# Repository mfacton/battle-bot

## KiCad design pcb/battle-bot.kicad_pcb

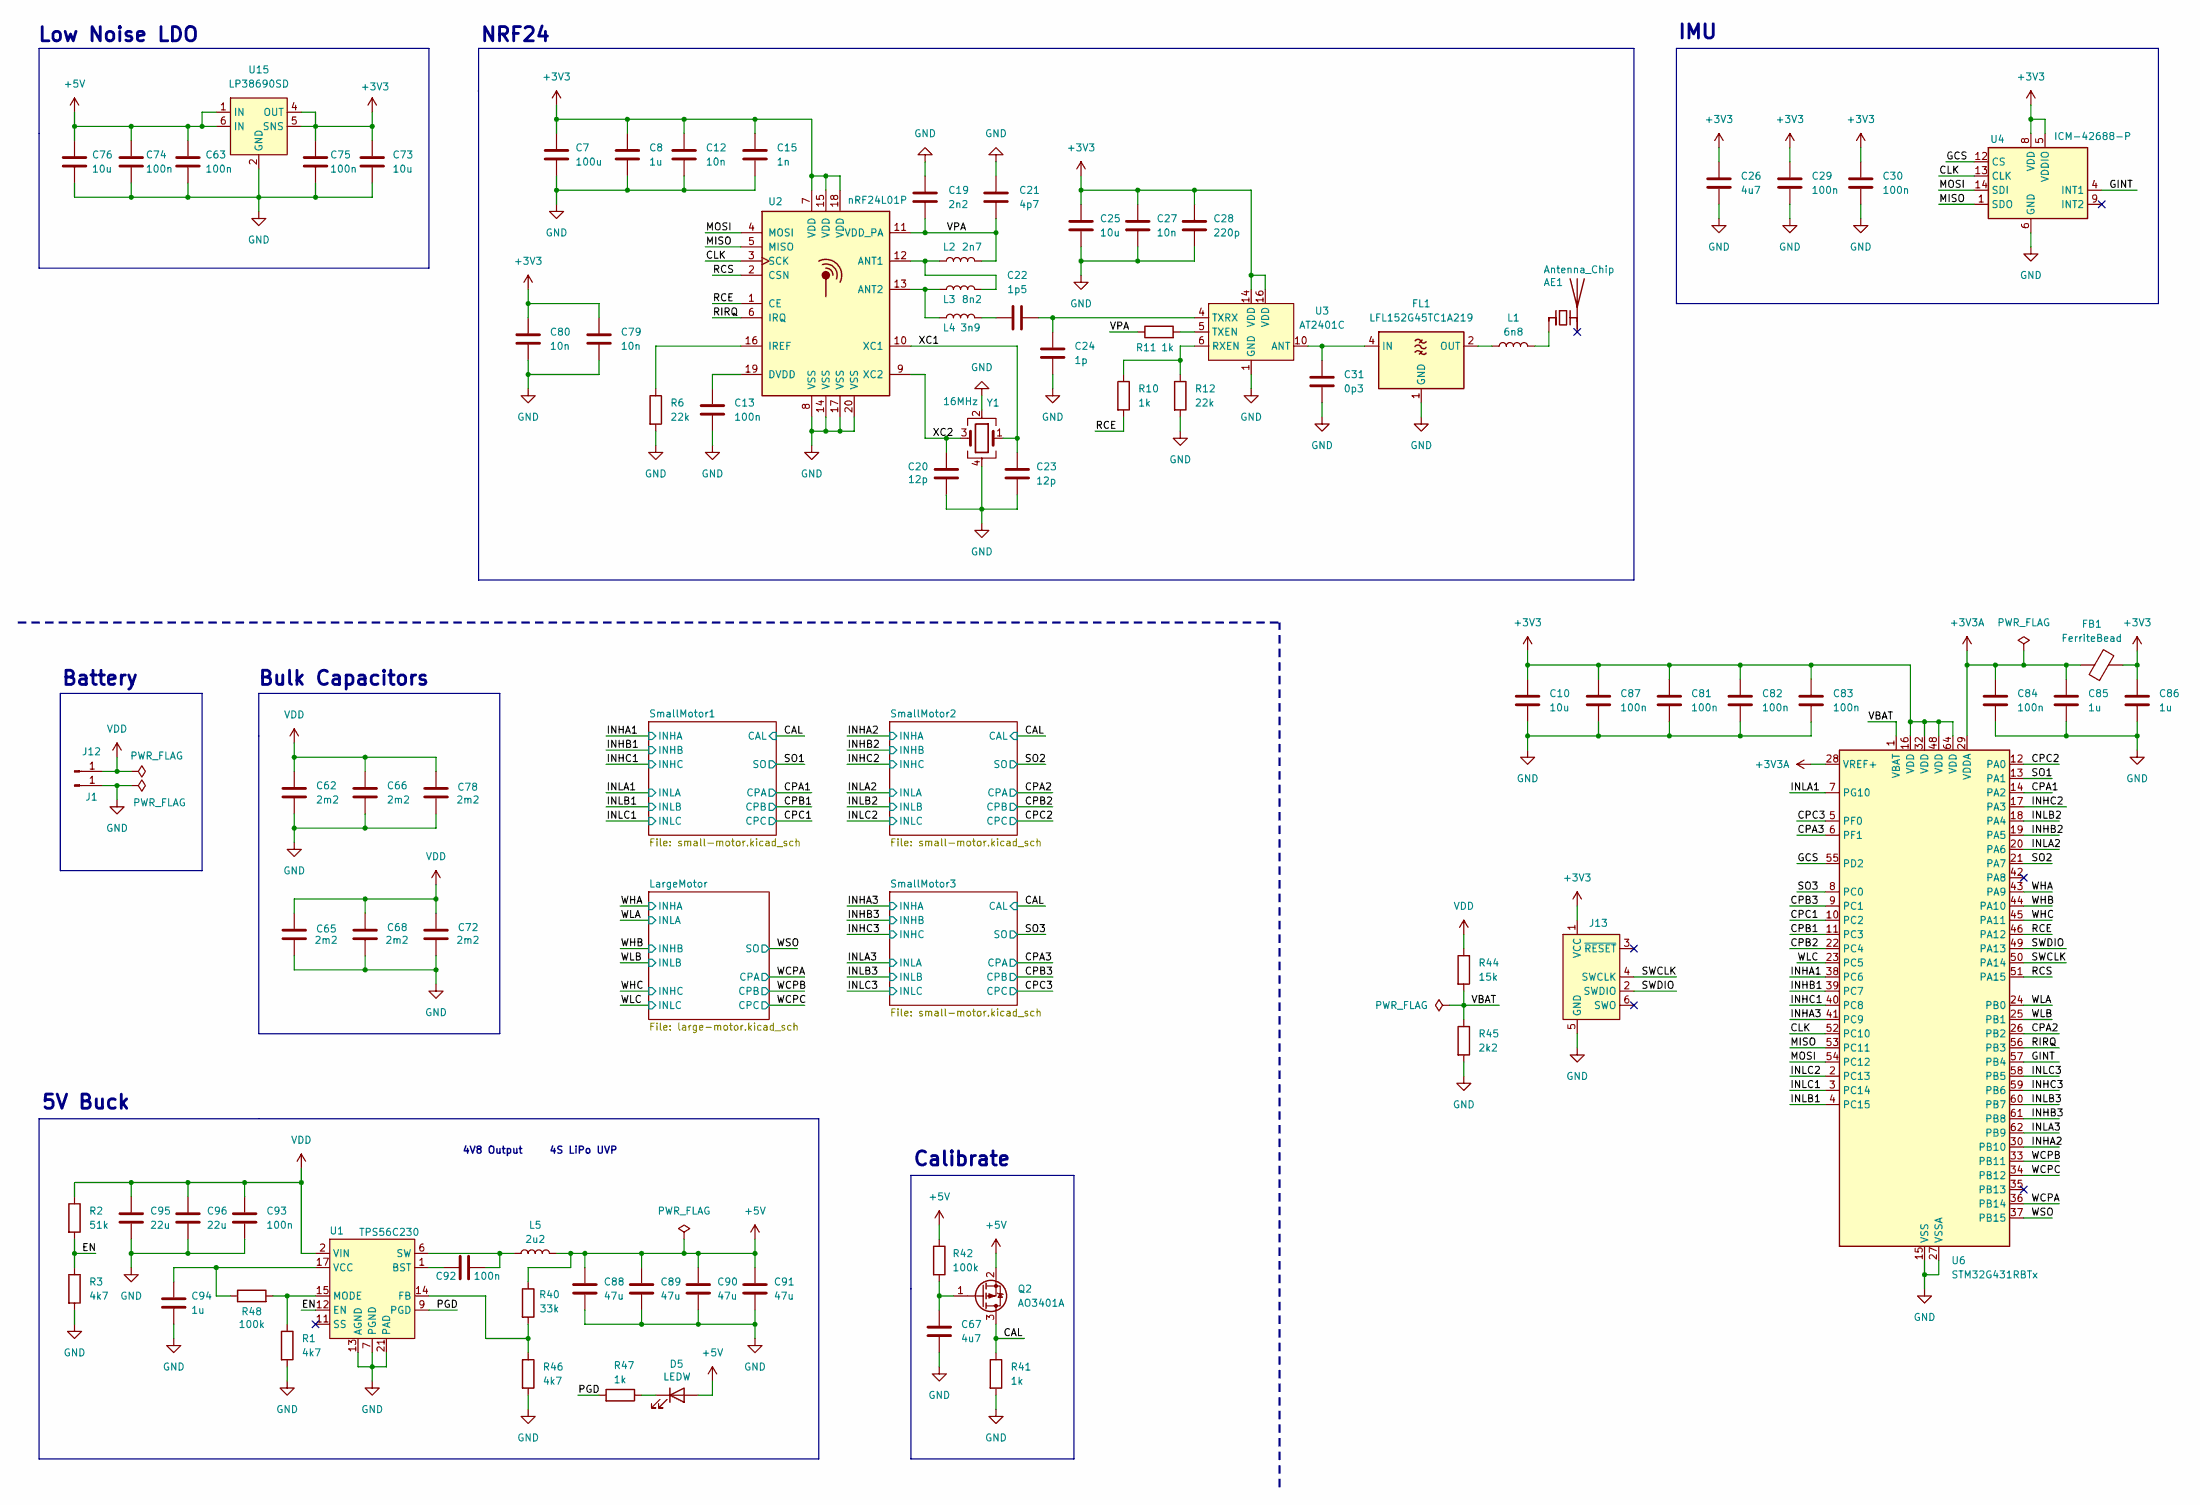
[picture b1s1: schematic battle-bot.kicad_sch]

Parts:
AE1: Antenna_Chip; Johanson_2450AT18x100; LCSC C127629
C7: 100u; C_1206_3216Metric; LCSC C15008
C8, C85, C86, C94: 1u; C_0402_1005Metric; LCSC C52923
C10, C25, C73: 10u; C_0402_1005Metric; LCSC C15525
C12, C27, C79, C80: 10n; C_0402_1005Metric; LCSC C15195
C13, C29, C30, C63, C74, C75, C81, C82, C83, C84, C87, C92: 100n; C_0402_1005Metric; LCSC C1525
C15: 1n; C_0402_1005Metric; LCSC C1523
C19: 2n2; C_0402_1005Metric; LCSC C1531
C20, C23: 12p; C_0402_1005Metric; LCSC C1547
C21: 4p7; C_0402_1005Metric; LCSC C1569
C22: 1p5; C_0402_1005Metric; LCSC C1552
C24: 1p; C_0402_1005Metric; LCSC C1550
C26, C67: 4u7; C_0402_1005Metric; LCSC C23733
C28: 220p; C_0402_1005Metric; LCSC C1530
C31: 0p3; C_0402_1005Metric; LCSC C880415
C62, C65, C66, C68, C72, C78: 2m2; C_D10xL16_Horizontal; LCSC C5438720
C76: 10u; C_0603_1608Metric; LCSC C19702
C88, C89, C90, C91: 47u; C_1206_3216Metric; LCSC C96123
C93: 100n; C_0402_1005Metric; LCSC C307331
C95, C96: 22u; C_0805_2012Metric; LCSC C45783
D5: LEDW; LED_0603_1608Metric; LCSC C2290
FB1: FerriteBead; L_0805_2012Metric; LCSC C1017
FL1: LFL152G45TC1A219; LCSC C91610
J1, J12: Conn_01x01_Pin; MountingHole_3.2mm_M3_Pad_Via
J13: Conn_ARM_SWD_TagConnect_TC2030-NL; Tag-Connect_TC2030-IDC-NL_2x03_P1.27mm_Vertical
L1: 6n8; L_0402_1005Metric; LCSC C82919
L2: 2n7; L_0402_1005Metric; LCSC C162541
L3: 8n2; L_0402_1005Metric; LCSC C84404
L4: 3n9; L_0402_1005Metric; LCSC C14033
L5: 2u2; L_Chilisin_BMRB00060618; LCSC C216189
Q2: AO3401A; SOT-23; LCSC C15127
R1, R3, R46: 4k7; R_0402_1005Metric; LCSC C25900
R2: 51k; R_0402_1005Metric; LCSC C25794
R6, R12: 22k; R_0402_1005Metric; LCSC C25768
R10, R11, R41, R47: 1k; R_0402_1005Metric; LCSC C11702
R40: 33k; R_0402_1005Metric; LCSC C25779
R42, R48: 100k; R_0402_1005Metric; LCSC C25741
R44: 15k; R_0402_1005Metric; LCSC C25756
R45: 2k2; R_0402_1005Metric; LCSC C25879
U1: TPS56C230; VQFN-20_3x3mm_P0.45; LCSC C1849534
U2: nRF24L01P; QFN-20-1EP_4x4mm_P0.5mm_EP2.5x2.5mm; LCSC C8791
U3: AT2401C; QFN-16-1EP_3x3mm_P0.5mm_EP1.7x1.7mm; LCSC C783588
U4: ICM-42688-P; LGA-14_3x2.5mm_P0.5mm_LayoutBorder3x4y
U6: STM32G431RBTx; LQFP-64_10x10mm_P0.5mm; LCSC C431633
U15: LP38690SD; DFN-6-1EP_3x3mm_P0.95mm_EP1.7x2.6mm; LCSC C130003
Y1: 16MHz; Crystal_SMD_3225-4Pin_3.2x2.5mm; LCSC C13738

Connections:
+3V3: C7.1, C8.1, C10.1, C12.1, C15.1, C25.1, C26.1, C27.1, C28.1, C29.1, C30.1, C73.1, C75.1, C79.1, C80.1, C81.1, C82.1, C83.1, C86.1, C87.1, FB1.2, J13.1 (VCC), U2.7 (VDD), U2.15 (VDD), U2.18 (VDD), U3.14 (VDD), U3.16 (VDD), U4.5 (VDDIO), U4.8 (VDD), U6.16 (VDD), U6.32 (VDD), U6.48 (VDD), U6.64 (VDD), U15.4 (OUT), U15.5 (SNS); also elsewhere on the board
+3V3A: C84.1, C85.1, FB1.1, U6.28 (VREF+), U6.29 (VDDA)
+5V: C63.1, C74.1, C76.1, C88.1, C89.1, C90.1, C91.1, D5.2 (A), L5.2, Q2.2 (S), R40.1, R42.1, U15.1 (IN), U15.6 (IN); also elsewhere on the board
/CAL: Q2.3 (D), R41.1; also elsewhere on the board
/CLK: U2.3 (SCK), U4.13 (CLK), U6.52 (PC10)
/CPA1: U6.14 (PA2); also elsewhere on the board
/CPA2: U6.26 (PB2); also elsewhere on the board
/CPA3: U6.6 (PF1); also elsewhere on the board
/CPB1: U6.11 (PC3); also elsewhere on the board
/CPB2: U6.22 (PC4); also elsewhere on the board
/CPB3: U6.9 (PC1); also elsewhere on the board
/CPC1: U6.10 (PC2); also elsewhere on the board
/CPC2: U6.12 (PA0); also elsewhere on the board
/CPC3: U6.5 (PF0); also elsewhere on the board
/EN: R2.2, R3.1, U1.12 (EN)
/GCS: U4.12 (CS), U6.55 (PD2)
/GINT: U4.4 (INT1), U6.57 (PB4)
/INHA1: U6.38 (PC6); also elsewhere on the board
/INHA2: U6.30 (PB10); also elsewhere on the board
/INHA3: U6.41 (PC9); also elsewhere on the board
/INHB1: U6.39 (PC7); also elsewhere on the board
/INHB2: U6.19 (PA5); also elsewhere on the board
/INHB3: U6.61 (PB8); also elsewhere on the board
/INHC1: U6.40 (PC8); also elsewhere on the board
/INHC2: U6.17 (PA3); also elsewhere on the board
/INHC3: U6.59 (PB6); also elsewhere on the board
/INLA1: U6.7 (PG10); also elsewhere on the board
/INLA2: U6.20 (PA6); also elsewhere on the board
/INLA3: U6.62 (PB9); also elsewhere on the board
/INLB1: U6.4 (PC15); also elsewhere on the board
/INLB2: U6.18 (PA4); also elsewhere on the board
/INLB3: U6.60 (PB7); also elsewhere on the board
/INLC1: U6.3 (PC14); also elsewhere on the board
/INLC2: U6.2 (PC13); also elsewhere on the board
/INLC3: U6.58 (PB5); also elsewhere on the board
/MISO: U2.5 (MISO), U4.1 (SDO), U6.53 (PC11)
/MOSI: U2.4 (MOSI), U4.14 (SDI), U6.54 (PC12)
/PGD: R47.2, U1.9 (PGD)
/RCE: R10.2, U2.1 (CE), U6.46 (PA12)
/RCS: U2.2 (CSN), U6.51 (PA15)
/RIRQ: U2.6 (IRQ), U6.56 (PB3)
/SO1: U6.13 (PA1); also elsewhere on the board
/SO2: U6.21 (PA7); also elsewhere on the board
/SO3: U6.8 (PC0); also elsewhere on the board
/SWCLK: J13.4 (SWCLK), U6.50 (PA14)
/SWDIO: J13.2 (SWDIO), U6.49 (PA13)
/VBAT: R44.2, R45.1, U6.1 (VBAT)
/VPA: C19.2, C21.1, L2.2, R11.1, U2.11 (VDD_PA)
/WCPA: U6.36 (PB14); also elsewhere on the board
/WCPB: U6.33 (PB11); also elsewhere on the board
/WCPC: U6.34 (PB12); also elsewhere on the board
/WHA: U6.43 (PA9); also elsewhere on the board
/WHB: U6.44 (PA10); also elsewhere on the board
/WHC: U6.45 (PA11); also elsewhere on the board
/WLA: U6.24 (PB0); also elsewhere on the board
/WLB: U6.25 (PB1); also elsewhere on the board
/WLC: U6.23 (PC5); also elsewhere on the board
/WSO: U6.37 (PB15); also elsewhere on the board
/XC1: C23.1, U2.10 (XC1), Y1.1
/XC2: C20.2, U2.9 (XC2), Y1.3
GND: C7.2, C8.2, C10.2, C12.2, C13.2, C15.2, C19.1, C20.1, C21.2, C23.2, C24.2, C25.2, C26.2, C27.2, C28.2, C29.2, C30.2, C31.2, C62.2, C63.2, C65.2, C66.1, C67.2, C68.2, C72.2, C73.2, C74.2, C75.2, C76.2, C78.2, C79.2, C80.2, C81.2, C82.2, C83.2, C84.2, C85.2, C86.2, C87.2, C88.2, C89.2, C90.2, C91.2, C93.2, C94.2, C95.2, C96.2, FL1.1 (GND), FL1.3 (GND), J1.1, J13.5 (GND), R1.2, R3.2, R6.2, R12.2, R41.2, R45.2, R46.2, U1.7 (PGND), U1.8 (PGND), U1.10 (NC), U1.13 (AGND), U1.16 (NC), U1.18 (PGND), U1.21 (PAD), U2.8 (VSS), U2.14 (VSS), U2.17 (VSS), U2.20 (VSS), U2.21 (VSS), U3.1 (GND), U3.2 (GND), U3.3 (GND), U3.7 (GND), U3.8 (GND), U3.9 (GND), U3.11 (GND), U3.12 (GND), U3.15 (GND), U3.17 (GND), U4.6 (GND), U4.7 (RESV), U4.11 (RESV), U6.15 (VSS), U6.27 (VSSA), U6.31 (VSS), U6.47 (VSS), U6.63 (VSS), U15.2 (GND), U15.7 (PAD), Y1.2, Y1.4; also elsewhere on the board
unnamed: AE1.1 (FEED), L1.2
unnamed: C22.1, L4.2
unnamed: C92.1, L5.1, U1.6 (SW), U1.19 (SW), U1.20 (SW)
unnamed: D5.1 (K), R47.1
unnamed: C31.1, FL1.4 (IN), U3.10 (ANT)
unnamed: FL1.2 (OUT), L1.1
unnamed: C67.1, Q2.1 (G), R42.2
unnamed: C92.2, U1.1 (BST)
unnamed: R40.2, R46.1, U1.14 (FB)
unnamed: R1.1, R48.2, U1.15 (MODE)
unnamed: C94.1, R48.1, U1.17 (VCC)
unnamed: L2.1, L3.2, U2.12 (ANT1)
unnamed: L3.1, L4.1, U2.13 (ANT2)
unnamed: C13.1, U2.19 (DVDD)
unnamed: R6.1, U2.16 (IREF)
unnamed: R10.1, R12.1, U3.6 (RXEN)
unnamed: R11.2, U3.5 (TXEN)
unnamed: C22.2, C24.1, U3.4 (TXRX)
VDD: C62.1, C65.1, C66.2, C68.1, C72.1, C78.1, C93.1, C95.1, C96.1, J12.1, R2.1, R44.1, U1.2 (VIN), U1.3 (VIN), U1.4 (VIN), U1.5 (VIN); also elsewhere on the board

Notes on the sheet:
Low Noise LDO
IMU
5V Buck
4S LiPo UVP
4V8 Output
Bulk Capacitors
Battery
Calibrate
NRF24

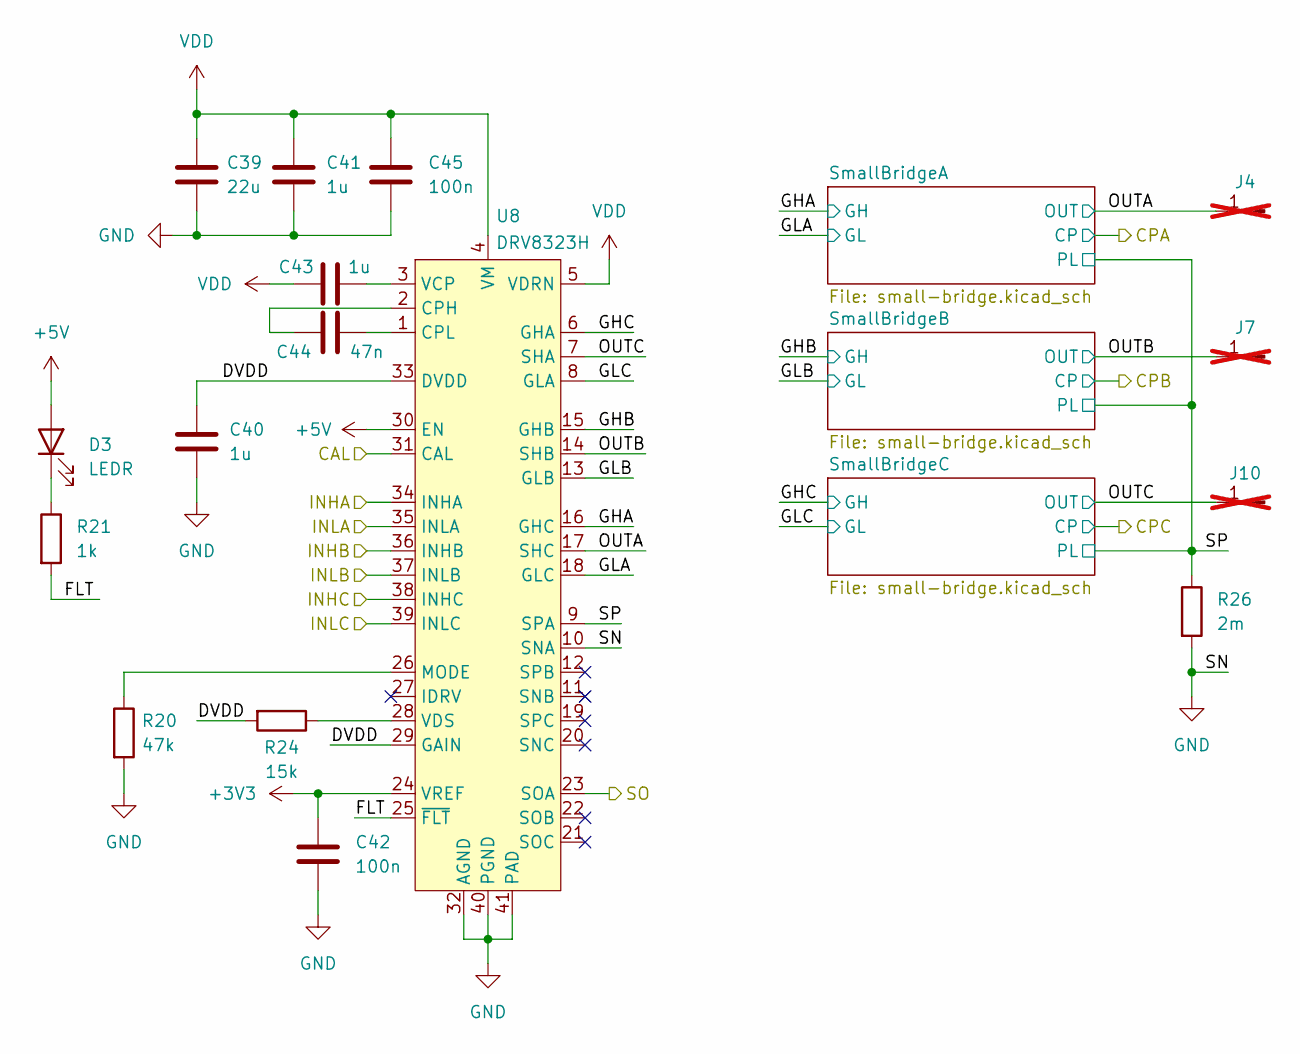
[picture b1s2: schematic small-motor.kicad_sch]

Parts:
C39: 22u; C_0805_2012Metric; LCSC C45783
C40, C43: 1u; C_0402_1005Metric; LCSC C52923
C41: 1u; R_0402_1005Metric; LCSC C52923
C42: 100n; C_0402_1005Metric; LCSC C1525
C44: 47n; C_0603_1608Metric; LCSC C1622
C45: 100n; C_0402_1005Metric; LCSC C307331
D3: LEDR; LED_0603_1608Metric; LCSC C2286
J4, J7, J10: Conn_01x01_Pin; Pad-P1.5; not fitted
R20: 47k; R_0402_1005Metric; LCSC C25792
R21: 1k; R_0402_1005Metric; LCSC C11702
R24: 15k; R_0402_1005Metric; LCSC C25756
R26: 2m; R_1206_3216Metric; LCSC C601094
U8: DRV8323H; HVQFN-40-1EP_6x6mm_P0.5mm_EP4.1x4.1mm; LCSC C701783

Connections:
+3V3: C42.1, U8.24 (VREF); also elsewhere on the board
+5V: D3.2 (A), U8.30 (EN); also elsewhere on the board
/CAL: U8.31 (CAL); also elsewhere on the board
/INHA2: U8.34 (INHA); also elsewhere on the board
/INHB2: U8.36 (INHB); also elsewhere on the board
/INHC2: U8.38 (INHC); also elsewhere on the board
/INLA2: U8.35 (INLA); also elsewhere on the board
/INLB2: U8.37 (INLB); also elsewhere on the board
/INLC2: U8.39 (INLC); also elsewhere on the board
/SO2: U8.23 (SOA); also elsewhere on the board
/SmallMotor2/DVDD: C40.1, R24.2, U8.29 (GAIN), U8.33 (DVDD)
/SmallMotor2/FLT: R21.2, U8.25 (~FLT)
/SmallMotor2/GHA: U8.16 (GHC); also elsewhere on the board
/SmallMotor2/GHB: U8.15 (GHB); also elsewhere on the board
/SmallMotor2/GHC: U8.6 (GHA); also elsewhere on the board
/SmallMotor2/GLA: U8.18 (GLC); also elsewhere on the board
/SmallMotor2/GLB: U8.13 (GLB); also elsewhere on the board
/SmallMotor2/GLC: U8.8 (GLA); also elsewhere on the board
/SmallMotor2/OUTA: J4.1, U8.17 (SHC); also elsewhere on the board
/SmallMotor2/OUTB: J7.1, U8.14 (SHB); also elsewhere on the board
/SmallMotor2/OUTC: J10.1, U8.7 (SHA); also elsewhere on the board
/SmallMotor2/SP: R26.1, U8.9 (SPA); also elsewhere on the board
GND: C39.2, C40.2, C41.2, C42.2, C45.2, R20.2, R26.2, U8.10 (SNA), U8.32 (AGND), U8.40 (PGND), U8.41 (PAD); also elsewhere on the board
unnamed: D3.1 (K), R21.1
unnamed: C44.1, U8.2 (CPH)
unnamed: C44.2, U8.1 (CPL)
unnamed: R20.1, U8.26 (MODE)
unnamed: C43.2, U8.3 (VCP)
unnamed: R24.1, U8.28 (VDS)
VDD: C39.1, C41.1, C43.1, C45.1, U8.4 (VM), U8.5 (VDRN); also elsewhere on the board

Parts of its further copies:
C32, C46: 22u; C_0805_2012Metric; LCSC C45783
C33, C36, C47, C50: 1u; C_0402_1005Metric; LCSC C52923
C34, C48: 1u; R_0402_1005Metric; LCSC C52923
C35, C49: 100n; C_0402_1005Metric; LCSC C1525
C37, C51: 47n; C_0603_1608Metric; LCSC C1622
C38, C52: 100n; C_0402_1005Metric; LCSC C307331
D2, D4: LEDR; LED_0603_1608Metric; LCSC C2286
J3, J5, J6, J8, J9, J11: Conn_01x01_Pin; Pad-P1.5; not fitted
R13, R27: 47k; R_0402_1005Metric; LCSC C25792
R14, R28: 1k; R_0402_1005Metric; LCSC C11702
R17, R31: 15k; R_0402_1005Metric; LCSC C25756
R19, R33: 2m; R_1206_3216Metric; LCSC C601094
U7, U9: DRV8323H; HVQFN-40-1EP_6x6mm_P0.5mm_EP4.1x4.1mm; LCSC C701783

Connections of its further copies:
+3V3: C35.1, C49.1, U7.24 (VREF), U9.24 (VREF); also elsewhere on the board
+5V: D2.2 (A), D4.2 (A), U7.30 (EN), U9.30 (EN); also elsewhere on the board
/CAL: U7.31 (CAL), U9.31 (CAL); also elsewhere on the board
/INHA1: U7.34 (INHA); also elsewhere on the board
/INHA3: U9.34 (INHA); also elsewhere on the board
/INHB1: U7.36 (INHB); also elsewhere on the board
/INHB3: U9.36 (INHB); also elsewhere on the board
/INHC1: U7.38 (INHC); also elsewhere on the board
/INHC3: U9.38 (INHC); also elsewhere on the board
/INLA1: U7.35 (INLA); also elsewhere on the board
/INLA3: U9.35 (INLA); also elsewhere on the board
/INLB1: U7.37 (INLB); also elsewhere on the board
/INLB3: U9.37 (INLB); also elsewhere on the board
/INLC1: U7.39 (INLC); also elsewhere on the board
/INLC3: U9.39 (INLC); also elsewhere on the board
/SO1: U7.23 (SOA); also elsewhere on the board
/SO3: U9.23 (SOA); also elsewhere on the board
/SmallMotor1/DVDD: C33.1, R17.2, U7.29 (GAIN), U7.33 (DVDD)
/SmallMotor1/FLT: R14.2, U7.25 (~FLT)
/SmallMotor1/GHA: U7.16 (GHC); also elsewhere on the board
/SmallMotor1/GHB: U7.15 (GHB); also elsewhere on the board
/SmallMotor1/GHC: U7.6 (GHA); also elsewhere on the board
/SmallMotor1/GLA: U7.18 (GLC); also elsewhere on the board
/SmallMotor1/GLB: U7.13 (GLB); also elsewhere on the board
/SmallMotor1/GLC: U7.8 (GLA); also elsewhere on the board
/SmallMotor1/OUTA: J3.1, U7.17 (SHC); also elsewhere on the board
/SmallMotor1/OUTB: J6.1, U7.14 (SHB); also elsewhere on the board
/SmallMotor1/OUTC: J9.1, U7.7 (SHA); also elsewhere on the board
/SmallMotor1/SP: R19.1, U7.9 (SPA); also elsewhere on the board
/SmallMotor3/DVDD: C47.1, R31.2, U9.29 (GAIN), U9.33 (DVDD)
/SmallMotor3/FLT: R28.2, U9.25 (~FLT)
/SmallMotor3/GHA: U9.16 (GHC); also elsewhere on the board
/SmallMotor3/GHB: U9.15 (GHB); also elsewhere on the board
/SmallMotor3/GHC: U9.6 (GHA); also elsewhere on the board
/SmallMotor3/GLA: U9.18 (GLC); also elsewhere on the board
/SmallMotor3/GLB: U9.13 (GLB); also elsewhere on the board
/SmallMotor3/GLC: U9.8 (GLA); also elsewhere on the board
/SmallMotor3/OUTA: J5.1, U9.17 (SHC); also elsewhere on the board
/SmallMotor3/OUTB: J8.1, U9.14 (SHB); also elsewhere on the board
/SmallMotor3/OUTC: J11.1, U9.7 (SHA); also elsewhere on the board
/SmallMotor3/SP: R33.1, U9.9 (SPA); also elsewhere on the board
GND: C32.2, C33.2, C34.2, C35.2, C38.2, C46.2, C47.2, C48.2, C49.2, C52.2, R13.2, R19.2, R27.2, R33.2, U7.10 (SNA), U7.32 (AGND), U7.40 (PGND), U7.41 (PAD), U9.10 (SNA), U9.32 (AGND), U9.40 (PGND), U9.41 (PAD); also elsewhere on the board
unnamed: D2.1 (K), R14.1
unnamed: D4.1 (K), R28.1
unnamed: C37.1, U7.2 (CPH)
unnamed: C37.2, U7.1 (CPL)
unnamed: R13.1, U7.26 (MODE)
unnamed: C36.2, U7.3 (VCP)
unnamed: R17.1, U7.28 (VDS)
unnamed: C51.1, U9.2 (CPH)
unnamed: C51.2, U9.1 (CPL)
unnamed: R27.1, U9.26 (MODE)
unnamed: C50.2, U9.3 (VCP)
unnamed: R31.1, U9.28 (VDS)
VDD: C32.1, C34.1, C36.1, C38.1, C46.1, C48.1, C50.1, C52.1, U7.4 (VM), U7.5 (VDRN), U9.4 (VM), U9.5 (VDRN); also elsewhere on the board

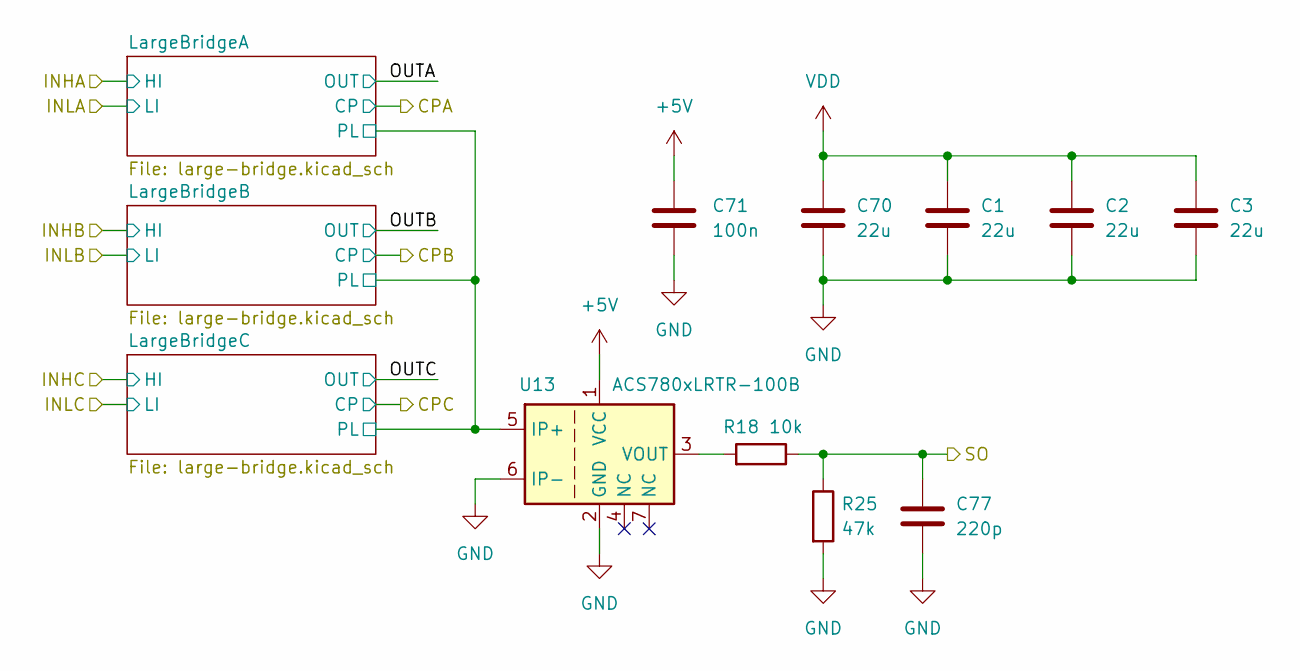
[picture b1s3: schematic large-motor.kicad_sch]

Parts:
C1, C2, C3, C70: 22u; C_0805_2012Metric; LCSC C45783
C71: 100n; C_0402_1005Metric; LCSC C1525
C77: 220p; R_0402_1005Metric; LCSC C1530
R18: 10k; R_0402_1005Metric; LCSC C25744
R25: 47k; R_0402_1005Metric; LCSC C25792
U13: ACS780xLRTR-100B; Allegro_PSOF-7_4.8x6.4mm_P1.60mm; LCSC C97317

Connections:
+5V: C71.1, U13.1 (VCC); also elsewhere on the board
/LargeMotor/LargeBridgeA/PL: U13.5 (IP+); also elsewhere on the board
/WSO: C77.1, R18.1, R25.1; also elsewhere on the board
GND: C1.2, C2.2, C3.2, C70.2, C71.2, C77.2, R25.2, U13.2 (GND), U13.6 (IP-); also elsewhere on the board
unnamed: R18.2, U13.3 (VOUT)
VDD: C1.1, C2.1, C3.1, C70.1; also elsewhere on the board

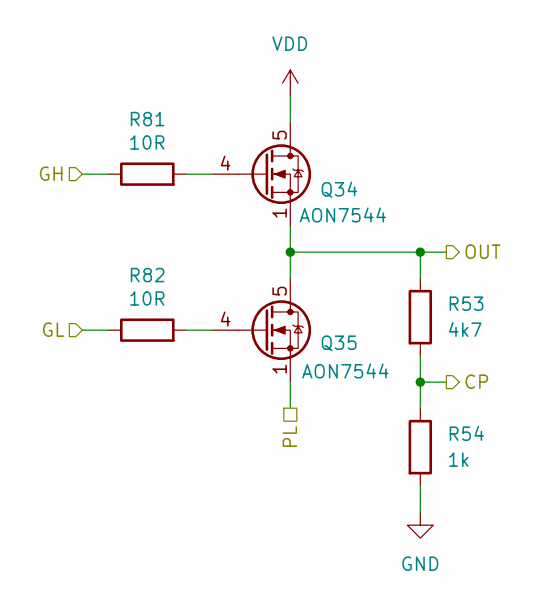
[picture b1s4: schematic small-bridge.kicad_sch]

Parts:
Q34, Q35: AON7544; DFN3x3A_8L_EP1_P; LCSC C315567
R53: 4k7; R_0402_1005Metric; LCSC C25900
R54: 1k; R_0402_1005Metric; LCSC C11702
R81, R82: 10R; R_0402_1005Metric; LCSC C25077

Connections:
/CPC2: R53.2, R54.1; also elsewhere on the board
/SmallMotor2/GHC: R81.1; also elsewhere on the board
/SmallMotor2/GLC: R82.1; also elsewhere on the board
/SmallMotor2/OUTC: Q34.1 (S), Q34.2 (S), Q34.3 (S), Q35.5 (D), Q35.6 (D), Q35.7 (D), Q35.8 (D), R53.1; also elsewhere on the board
/SmallMotor2/SP: Q35.1 (S), Q35.2 (S), Q35.3 (S); also elsewhere on the board
GND: R54.2; also elsewhere on the board
unnamed: Q34.4 (G), R81.2
unnamed: Q35.4 (G), R82.2
VDD: Q34.5 (D), Q34.6 (D), Q34.7 (D), Q34.8 (D); also elsewhere on the board

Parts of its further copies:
Q1, Q27, Q28, Q29, Q30, Q31, Q32, Q33, Q36, Q37, Q38, Q39, Q40, Q41, Q42, Q43: AON7544; DFN3x3A_8L_EP1_P; LCSC C315567
R49, R51, R55, R57, R59, R64, R66, R71: 4k7; R_0402_1005Metric; LCSC C25900
R50, R52, R56, R58, R60, R65, R70, R72: 1k; R_0402_1005Metric; LCSC C11702
R73, R74, R75, R76, R77, R78, R79, R80, R83, R84, R85, R86, R87, R88, R89, R90: 10R; R_0402_1005Metric; LCSC C25077

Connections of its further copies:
/CPA1: R57.2, R58.1; also elsewhere on the board
/CPA2: R59.2, R60.1; also elsewhere on the board
/CPA3: R64.2, R65.1; also elsewhere on the board
/CPB1: R66.2, R70.1; also elsewhere on the board
/CPB2: R71.2, R72.1; also elsewhere on the board
/CPB3: R49.2, R50.1; also elsewhere on the board
/CPC1: R51.2, R52.1; also elsewhere on the board
/CPC3: R55.2, R56.1; also elsewhere on the board
/SmallMotor1/GHA: R85.1; also elsewhere on the board
/SmallMotor1/GHB: R75.1; also elsewhere on the board
/SmallMotor1/GHC: R79.1; also elsewhere on the board
/SmallMotor1/GLA: R86.1; also elsewhere on the board
/SmallMotor1/GLB: R76.1; also elsewhere on the board
/SmallMotor1/GLC: R80.1; also elsewhere on the board
/SmallMotor1/OUTA: Q38.1 (S), Q38.2 (S), Q38.3 (S), Q39.5 (D), Q39.6 (D), Q39.7 (D), Q39.8 (D), R57.1; also elsewhere on the board
/SmallMotor1/OUTB: Q28.1 (S), Q28.2 (S), Q28.3 (S), Q29.5 (D), Q29.6 (D), Q29.7 (D), Q29.8 (D), R66.1; also elsewhere on the board
/SmallMotor1/OUTC: Q32.1 (S), Q32.2 (S), Q32.3 (S), Q33.5 (D), Q33.6 (D), Q33.7 (D), Q33.8 (D), R51.1; also elsewhere on the board
/SmallMotor1/SP: Q29.1 (S), Q29.2 (S), Q29.3 (S), Q33.1 (S), Q33.2 (S), Q33.3 (S), Q39.1 (S), Q39.2 (S), Q39.3 (S); also elsewhere on the board
/SmallMotor2/GHA: R87.1; also elsewhere on the board
/SmallMotor2/GHB: R77.1; also elsewhere on the board
/SmallMotor2/GLA: R88.1; also elsewhere on the board
/SmallMotor2/GLB: R78.1; also elsewhere on the board
/SmallMotor2/OUTA: Q40.1 (S), Q40.2 (S), Q40.3 (S), Q41.5 (D), Q41.6 (D), Q41.7 (D), Q41.8 (D), R59.1; also elsewhere on the board
/SmallMotor2/OUTB: Q30.1 (S), Q30.2 (S), Q30.3 (S), Q31.5 (D), Q31.6 (D), Q31.7 (D), Q31.8 (D), R71.1; also elsewhere on the board
/SmallMotor2/SP: Q31.1 (S), Q31.2 (S), Q31.3 (S), Q41.1 (S), Q41.2 (S), Q41.3 (S); also elsewhere on the board
/SmallMotor3/GHA: R89.1; also elsewhere on the board
/SmallMotor3/GHB: R73.1; also elsewhere on the board
/SmallMotor3/GHC: R83.1; also elsewhere on the board
/SmallMotor3/GLA: R90.1; also elsewhere on the board
/SmallMotor3/GLB: R74.1; also elsewhere on the board
/SmallMotor3/GLC: R84.1; also elsewhere on the board
/SmallMotor3/OUTA: Q42.1 (S), Q42.2 (S), Q42.3 (S), Q43.5 (D), Q43.6 (D), Q43.7 (D), Q43.8 (D), R64.1; also elsewhere on the board
/SmallMotor3/OUTB: Q1.1 (S), Q1.2 (S), Q1.3 (S), Q27.5 (D), Q27.6 (D), Q27.7 (D), Q27.8 (D), R49.1; also elsewhere on the board
/SmallMotor3/OUTC: Q36.1 (S), Q36.2 (S), Q36.3 (S), Q37.5 (D), Q37.6 (D), Q37.7 (D), Q37.8 (D), R55.1; also elsewhere on the board
/SmallMotor3/SP: Q27.1 (S), Q27.2 (S), Q27.3 (S), Q37.1 (S), Q37.2 (S), Q37.3 (S), Q43.1 (S), Q43.2 (S), Q43.3 (S); also elsewhere on the board
GND: R50.2, R52.2, R56.2, R58.2, R60.2, R65.2, R70.2, R72.2; also elsewhere on the board
unnamed: Q1.4 (G), R73.2
unnamed: Q27.4 (G), R74.2
unnamed: Q28.4 (G), R75.2
unnamed: Q29.4 (G), R76.2
unnamed: Q30.4 (G), R77.2
unnamed: Q31.4 (G), R78.2
unnamed: Q32.4 (G), R79.2
unnamed: Q33.4 (G), R80.2
unnamed: Q36.4 (G), R83.2
unnamed: Q37.4 (G), R84.2
unnamed: Q38.4 (G), R85.2
unnamed: Q39.4 (G), R86.2
unnamed: Q40.4 (G), R87.2
unnamed: Q41.4 (G), R88.2
unnamed: Q42.4 (G), R89.2
unnamed: Q43.4 (G), R90.2
VDD: Q1.5 (D), Q1.6 (D), Q1.7 (D), Q1.8 (D), Q28.5 (D), Q28.6 (D), Q28.7 (D), Q28.8 (D), Q30.5 (D), Q30.6 (D), Q30.7 (D), Q30.8 (D), Q32.5 (D), Q32.6 (D), Q32.7 (D), Q32.8 (D), Q36.5 (D), Q36.6 (D), Q36.7 (D), Q36.8 (D), Q38.5 (D), Q38.6 (D), Q38.7 (D), Q38.8 (D), Q40.5 (D), Q40.6 (D), Q40.7 (D), Q40.8 (D), Q42.5 (D), Q42.6 (D), Q42.7 (D), Q42.8 (D); also elsewhere on the board

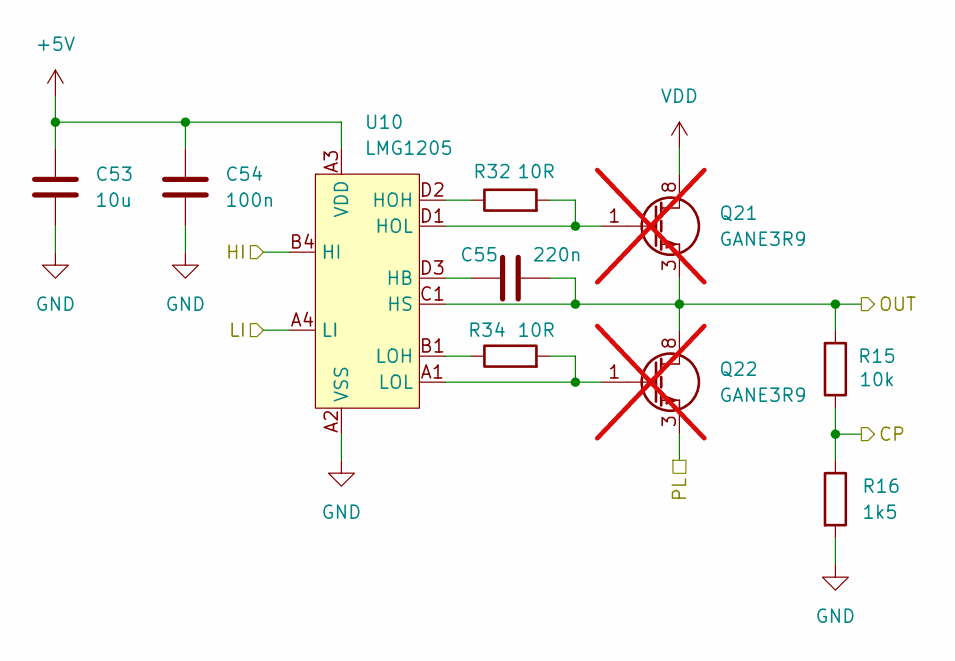
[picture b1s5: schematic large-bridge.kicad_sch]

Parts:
C53: 10u; C_0603_1608Metric; LCSC C19702
C54: 100n; C_0402_1005Metric; LCSC C1525
C55: 220n; C_0402_1005Metric; LCSC C16772
Q21, Q22: GANE3R9; not fitted
R15: 10k; R_0402_1005Metric; LCSC C25744
R16: 1k5; R_0402_1005Metric; LCSC C25867
R32, R34: 10R; R_0402_1005Metric; LCSC C25077
U10: LMG1205; LCSC C2653814

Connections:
+5V: C53.1, C54.1, U10.A3 (VDD), U10.C4 (VDD); also elsewhere on the board
/LargeMotor/LargeBridgeA/PL: Q22.3 (S), Q22.4 (S), Q22.5 (S), Q22.6 (S), Q22.7 (S), Q22.9 (S), Q22.11 (S), Q22.21 (S), Q22.23 (S); also elsewhere on the board
/LargeMotor/OUTA: C55.2, Q21.3 (S), Q21.4 (S), Q21.5 (S), Q21.6 (S), Q21.7 (S), Q21.9 (S), Q21.11 (S), Q21.21 (S), Q21.23 (S), Q22.8 (D), Q22.10 (D), Q22.12 (D), Q22.13 (D), Q22.14 (D), Q22.15 (D), Q22.16 (D), Q22.17 (D), Q22.18 (D), Q22.19 (D), Q22.20 (D), Q22.22 (D), Q22.24 (D), R15.2, U10.C1 (HS), U10.D4 (HS)
/WCPA: R15.1, R16.1; also elsewhere on the board
/WHA: U10.B4 (HI); also elsewhere on the board
/WLA: U10.A4 (LI); also elsewhere on the board
GND: C53.2, C54.2, R16.2, U10.A2 (VSS); also elsewhere on the board
unnamed: C55.1, U10.D3 (HB)
unnamed: R32.1, U10.D2 (HOH)
unnamed: Q21.1 (G), Q21.2 (G), Q21.25 (G), R32.2, U10.D1 (HOL)
unnamed: R34.1, U10.B1 (LOH)
unnamed: Q22.1 (G), Q22.2 (G), Q22.25 (G), R34.2, U10.A1 (LOL)
VDD: Q21.8 (D), Q21.10 (D), Q21.12 (D), Q21.13 (D), Q21.14 (D), Q21.15 (D), Q21.16 (D), Q21.17 (D), Q21.18 (D), Q21.19 (D), Q21.20 (D), Q21.22 (D), Q21.24 (D); also elsewhere on the board

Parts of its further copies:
C56, C59: 10u; C_0603_1608Metric; LCSC C19702
C57, C60: 100n; C_0402_1005Metric; LCSC C1525
C58, C61: 220n; C_0402_1005Metric; LCSC C16772
Q23, Q24, Q25, Q26: GANE3R9; not fitted
R22, R29: 10k; R_0402_1005Metric; LCSC C25744
R23, R30: 1k5; R_0402_1005Metric; LCSC C25867
R35, R36, R37, R38: 10R; R_0402_1005Metric; LCSC C25077
U11, U12: LMG1205; LCSC C2653814

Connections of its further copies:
+5V: C56.1, C57.1, C59.1, C60.1, U11.A3 (VDD), U11.C4 (VDD), U12.A3 (VDD), U12.C4 (VDD); also elsewhere on the board
/LargeMotor/LargeBridgeA/PL: Q24.3 (S), Q24.4 (S), Q24.5 (S), Q24.6 (S), Q24.7 (S), Q24.9 (S), Q24.11 (S), Q24.21 (S), Q24.23 (S), Q26.3 (S), Q26.4 (S), Q26.5 (S), Q26.6 (S), Q26.7 (S), Q26.9 (S), Q26.11 (S), Q26.21 (S), Q26.23 (S); also elsewhere on the board
/LargeMotor/OUTB: C58.2, Q23.3 (S), Q23.4 (S), Q23.5 (S), Q23.6 (S), Q23.7 (S), Q23.9 (S), Q23.11 (S), Q23.21 (S), Q23.23 (S), Q24.8 (D), Q24.10 (D), Q24.12 (D), Q24.13 (D), Q24.14 (D), Q24.15 (D), Q24.16 (D), Q24.17 (D), Q24.18 (D), Q24.19 (D), Q24.20 (D), Q24.22 (D), Q24.24 (D), R22.2, U11.C1 (HS), U11.D4 (HS)
/LargeMotor/OUTC: C61.2, Q25.3 (S), Q25.4 (S), Q25.5 (S), Q25.6 (S), Q25.7 (S), Q25.9 (S), Q25.11 (S), Q25.21 (S), Q25.23 (S), Q26.8 (D), Q26.10 (D), Q26.12 (D), Q26.13 (D), Q26.14 (D), Q26.15 (D), Q26.16 (D), Q26.17 (D), Q26.18 (D), Q26.19 (D), Q26.20 (D), Q26.22 (D), Q26.24 (D), R29.2, U12.C1 (HS), U12.D4 (HS)
/WCPB: R22.1, R23.1; also elsewhere on the board
/WCPC: R29.1, R30.1; also elsewhere on the board
/WHB: U11.B4 (HI); also elsewhere on the board
/WHC: U12.B4 (HI); also elsewhere on the board
/WLB: U11.A4 (LI); also elsewhere on the board
/WLC: U12.A4 (LI); also elsewhere on the board
GND: C56.2, C57.2, C59.2, C60.2, R23.2, R30.2, U11.A2 (VSS), U12.A2 (VSS); also elsewhere on the board
unnamed: C58.1, U11.D3 (HB)
unnamed: R35.1, U11.D2 (HOH)
unnamed: Q23.1 (G), Q23.2 (G), Q23.25 (G), R35.2, U11.D1 (HOL)
unnamed: R36.1, U11.B1 (LOH)
unnamed: Q24.1 (G), Q24.2 (G), Q24.25 (G), R36.2, U11.A1 (LOL)
unnamed: C61.1, U12.D3 (HB)
unnamed: R37.1, U12.D2 (HOH)
unnamed: Q25.1 (G), Q25.2 (G), Q25.25 (G), R37.2, U12.D1 (HOL)
unnamed: R38.1, U12.B1 (LOH)
unnamed: Q26.1 (G), Q26.2 (G), Q26.25 (G), R38.2, U12.A1 (LOL)
VDD: Q23.8 (D), Q23.10 (D), Q23.12 (D), Q23.13 (D), Q23.14 (D), Q23.15 (D), Q23.16 (D), Q23.17 (D), Q23.18 (D), Q23.19 (D), Q23.20 (D), Q23.22 (D), Q23.24 (D), Q25.8 (D), Q25.10 (D), Q25.12 (D), Q25.13 (D), Q25.14 (D), Q25.15 (D), Q25.16 (D), Q25.17 (D), Q25.18 (D), Q25.19 (D), Q25.20 (D), Q25.22 (D), Q25.24 (D); also elsewhere on the board
